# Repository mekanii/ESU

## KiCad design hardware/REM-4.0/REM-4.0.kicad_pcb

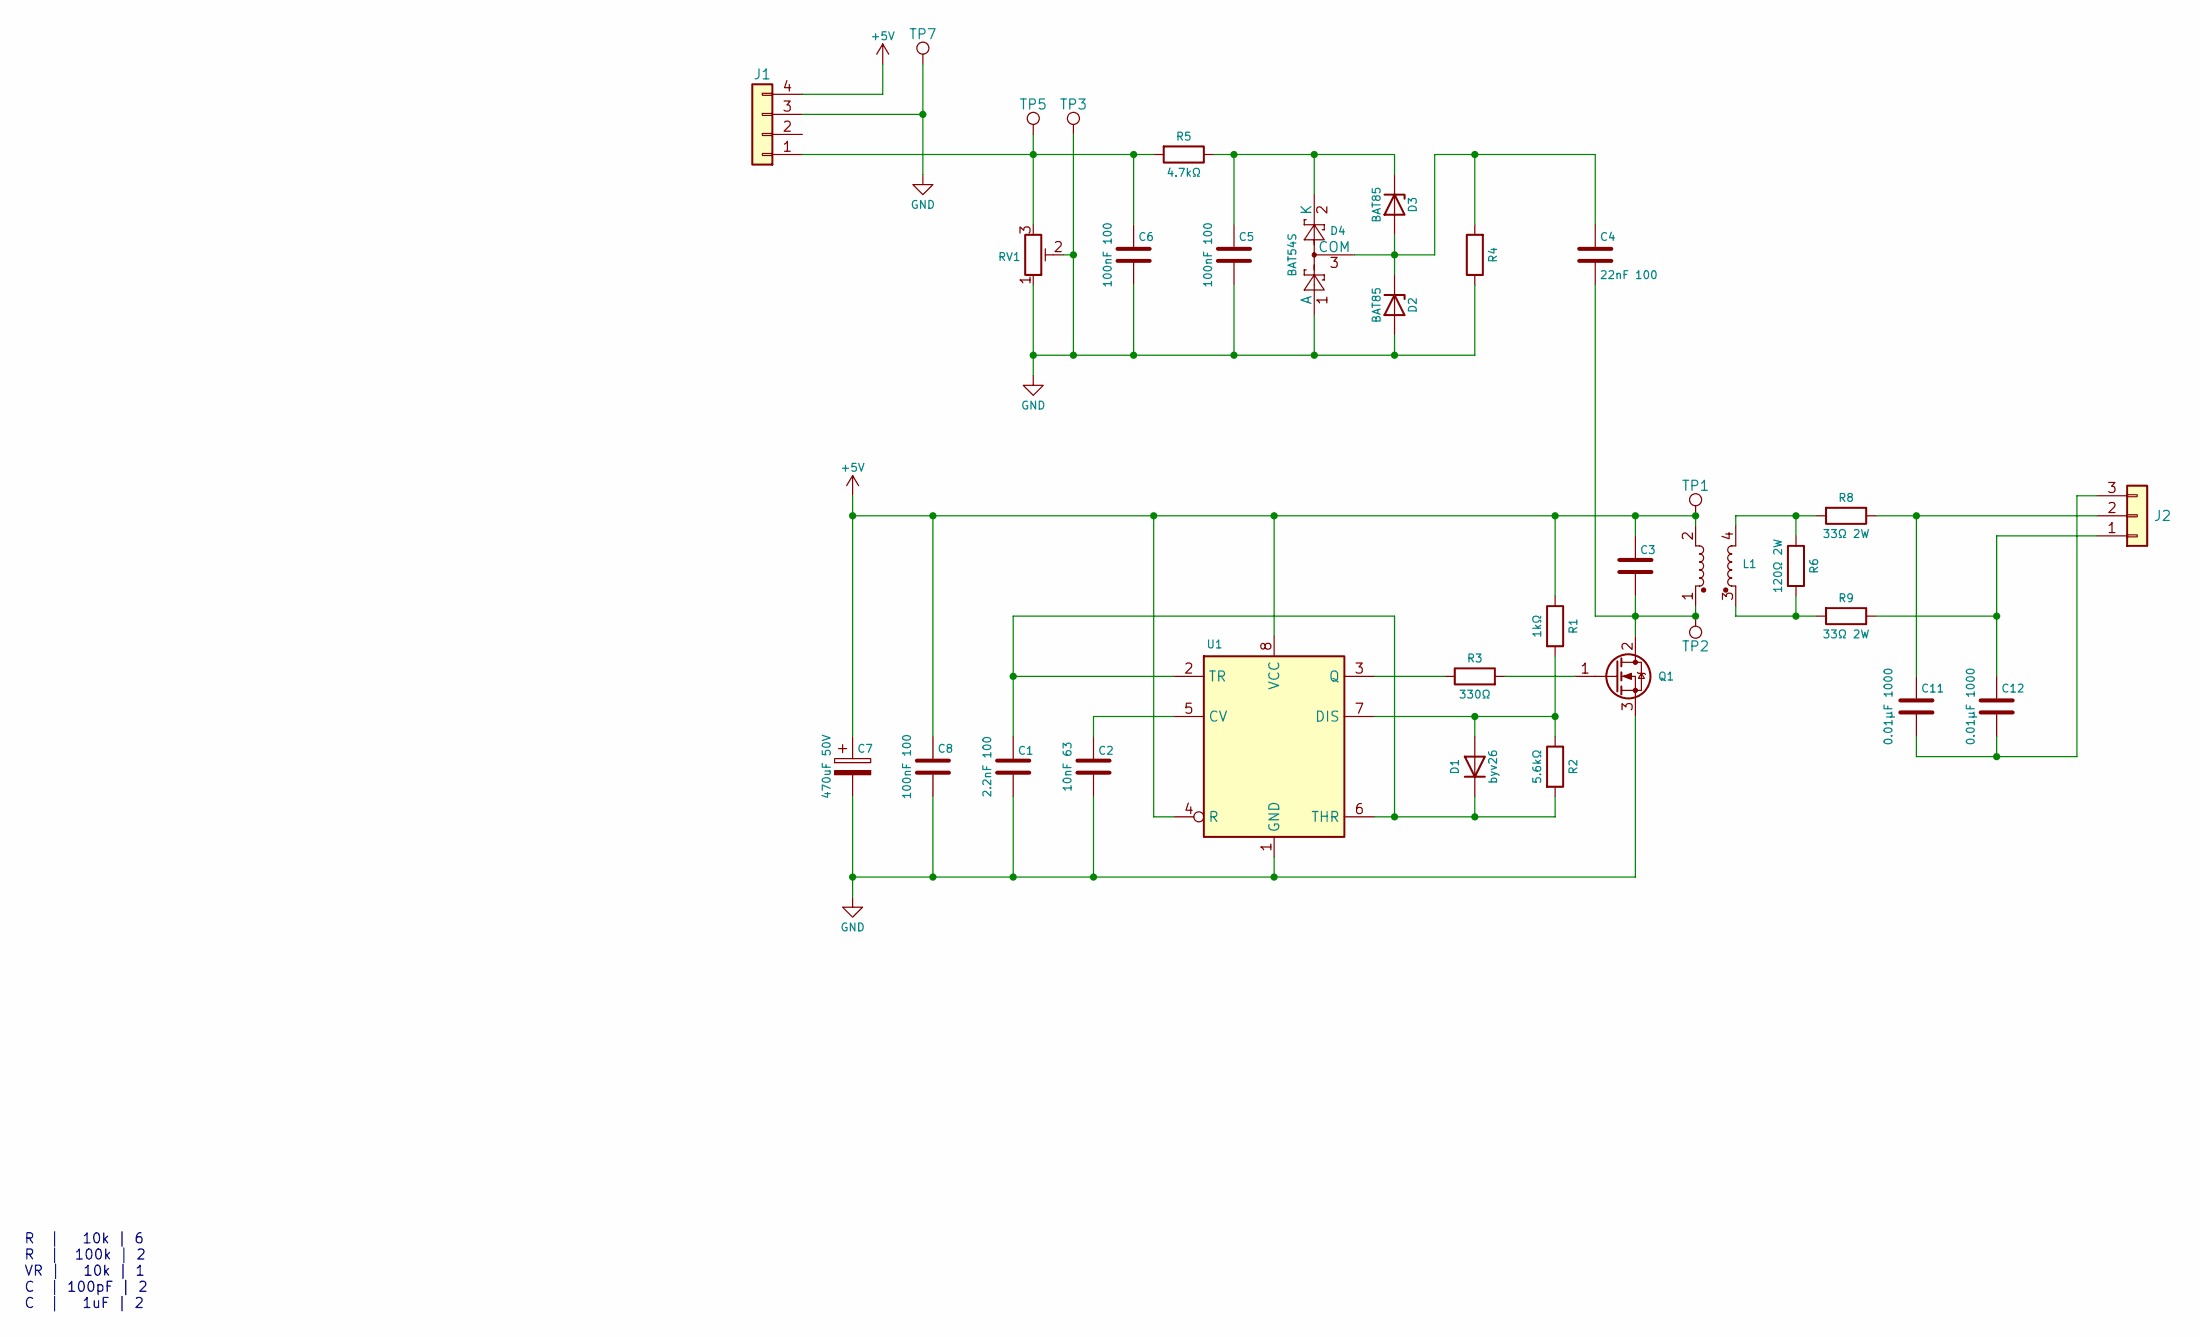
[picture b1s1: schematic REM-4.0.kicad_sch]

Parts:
C1: 2.2nF 100; C_Rect_L7.0mm_W3.5mm_P5.00mm
C2: 10nF 63; C_Rect_L7.0mm_W3.5mm_P5.00mm
C3: 0.022µF 400V; C_Rect_L13.0mm_W5.0mm_P10.00mm_FKS3_FKP3_MKS4
C4: 22nF 100; C_Rect_L7.0mm_W3.5mm_P5.00mm
C5, C6, C8: 100nF 100; C_Rect_L7.0mm_W3.5mm_P5.00mm
C7: 470uF 50V; CP_Radial_D12.5mm_P5.00mm
C11, C12: 0.01µF 1000; C_Rect_L13.0mm_W5.0mm_P10.00mm_FKS3_FKP3_MKS4
D1: byv26; D_DO-35_SOD27_P7.62mm_Horizontal
D2, D3: BAT85; D_DO-34_SOD68_P7.62mm_Horizontal
D4: BAT54S; SOT-23
J1: PinHeader_2.54mm 02x04 Horizontal; PinHeader_1x04_P2.54mm_Horizontal_2
J2: PinHeader_2.54mm 02x05 Horizontal; PinHeader_1x03_P5.08mm_Horizontal_2
L1: Isolated Transformer (Custom); L_CommonMode_Toroid_Horizontal_OD23mm_ID14mm_H8mm
Q1: IRLB3034PbF; TO-220-3_Horizontal_TabDown
R1: 1kΩ; R_Axial_DIN0204_L3.6mm_D1.6mm_P7.62mm_Horizontal
R2: 5.6kΩ; R_Axial_DIN0204_L3.6mm_D1.6mm_P7.62mm_Horizontal
R3: 330Ω; R_Axial_DIN0204_L3.6mm_D1.6mm_P7.62mm_Horizontal
R4: 10k; R_Axial_DIN0204_L3.6mm_D1.6mm_P7.62mm_Horizontal
R5: 4.7kΩ; R_Axial_DIN0204_L3.6mm_D1.6mm_P7.62mm_Horizontal
R6: 120Ω 2W; R_Axial_DIN0414_L11.9mm_D4.5mm_P20.32mm_Horizontal
R8, R9: 33Ω 2W; R_Axial_DIN0414_L11.9mm_D4.5mm_P20.32mm_Horizontal
RV1: 5kΩ; Potentiometer_Bourns_3296X_Horizontal
TP1, TP2, TP3, TP5, TP7: TestPoint_Bridge_Pitch2.54mm_Drill1.0mm
U1: NE555P; DIP-8_W7.62mm_Socket

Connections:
+5V: C3.1, C7.1, C8.1, J1.4, L1.2, R1.1, TP1.1, U1.4 (R), U1.8 (VCC)
GND: C1.2, C2.2, C5.2, C6.2, C7.2, C8.2, D2.2 (A), D4.1 (A), J1.3, Q1.3 (S), R4.1, RV1.1, RV1.2, TP3.1, TP7.1, U1.1 (GND)
unnamed: D1.2 (A), R1.2, R2.1, U1.7 (DIS)
unnamed: C1.1, D1.1 (K), R2.2, U1.2 (TR), U1.6 (THR)
unnamed: C4.1, D2.1 (K), D3.2 (A), D4.3 (COM), R4.2
unnamed: C5.1, D3.1 (K), D4.2 (K), R5.1
unnamed: C6.1, J1.1, R5.2, RV1.3, TP5.1
unnamed: C12.1, J2.1, R9.1
unnamed: C11.1, J2.2, R8.1
unnamed: C11.2, C12.2, J2.3
unnamed: L1.3, R6.2, R9.2
unnamed: L1.4, R6.1, R8.2
unnamed: C3.2, C4.2, L1.1, Q1.2 (D), TP2.1
unnamed: Q1.1 (G), R3.2
unnamed: C2.1, U1.5 (CV)
unnamed: R3.1, U1.3 (Q)

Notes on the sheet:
R | 10k | 6 R | 100k | 2 VR | 10k | 1 C | 100pF | 2 C | 1uF | 2

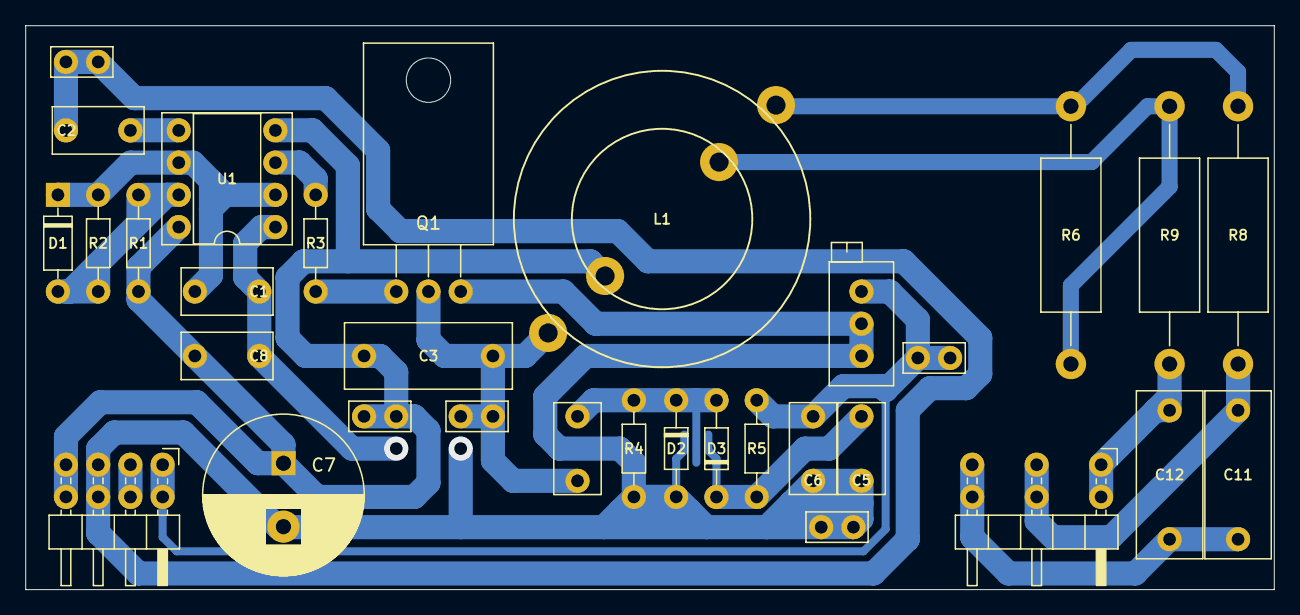
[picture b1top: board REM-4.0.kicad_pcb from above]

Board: 2 copper layers, 98.4 x 44.5 mm, 33 parts (1 on the bottom side), 16 nets.

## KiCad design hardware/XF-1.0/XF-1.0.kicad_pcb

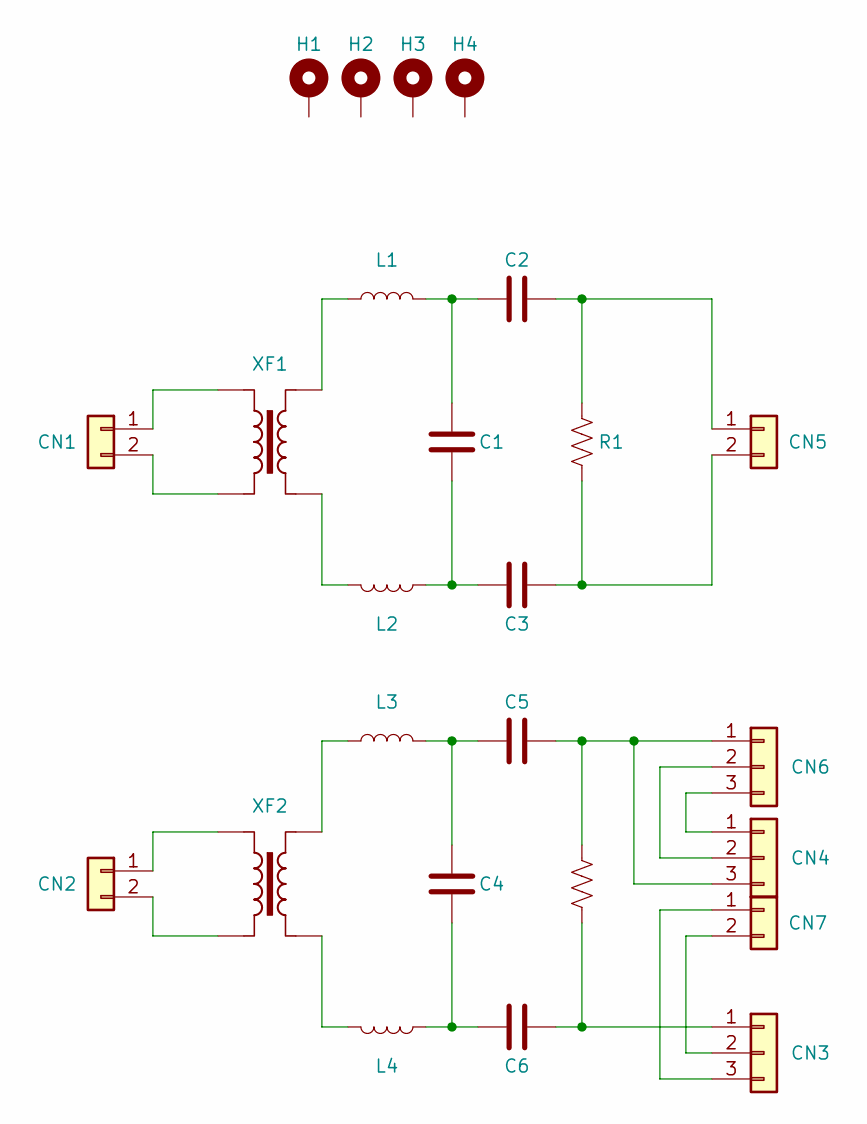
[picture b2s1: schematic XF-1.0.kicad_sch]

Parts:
C1, C4: 2.7nF; C_Axial_L12.0mm_D6.5mm_P20.00mm_Horizontal
C2, C3, C5, C6: 4.7nF; C_Rect_L13.0mm_W8.0mm_P10.00mm_FKS3_FKP3_MKS4
CN1, CN2, CN5, CN7: Conn_01x02; Molex_KK-396_5273-03A_1x03_P3.96mm_Vertical_2
CN3, CN4, CN6: Conn_01x03; Molex_KK-396_5273-05A_1x05_P3.96mm_Vertical_2
H1, H2, H3, H4: MountingHole_3mm_Pad
L1, L2, L3, L4: 29µH; L_Radial_Multilayer_D8.0mm_P12.70mm
R1, R2: RBTL
XF1, XF2: Transformer_Toroid_Horizontal_OD40_ID23_H15

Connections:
unnamed: C1.1, C2.1, L1.2
unnamed: C1.2, C3.1, L2.2
unnamed: C4.1, C5.1, L3.2
unnamed: C4.2, C6.1, L4.2
unnamed: CN1.1, XF1.1
unnamed: CN1.2, XF1.2
unnamed: CN2.1, XF2.1
unnamed: CN2.2, XF2.2
unnamed: C6.2, CN3.1, R2.2
unnamed: CN3.2, CN7.2
unnamed: CN3.3, CN7.1
unnamed: CN4.1, CN6.3
unnamed: CN4.2, CN6.2
unnamed: C5.2, CN4.3, CN6.1, R2.1
unnamed: C2.2, CN5.1, R1.1
unnamed: C3.2, CN5.2, R1.2
unnamed: L1.1, XF1.4
unnamed: L2.1, XF1.3
unnamed: L3.1, XF2.4
unnamed: L4.1, XF2.3

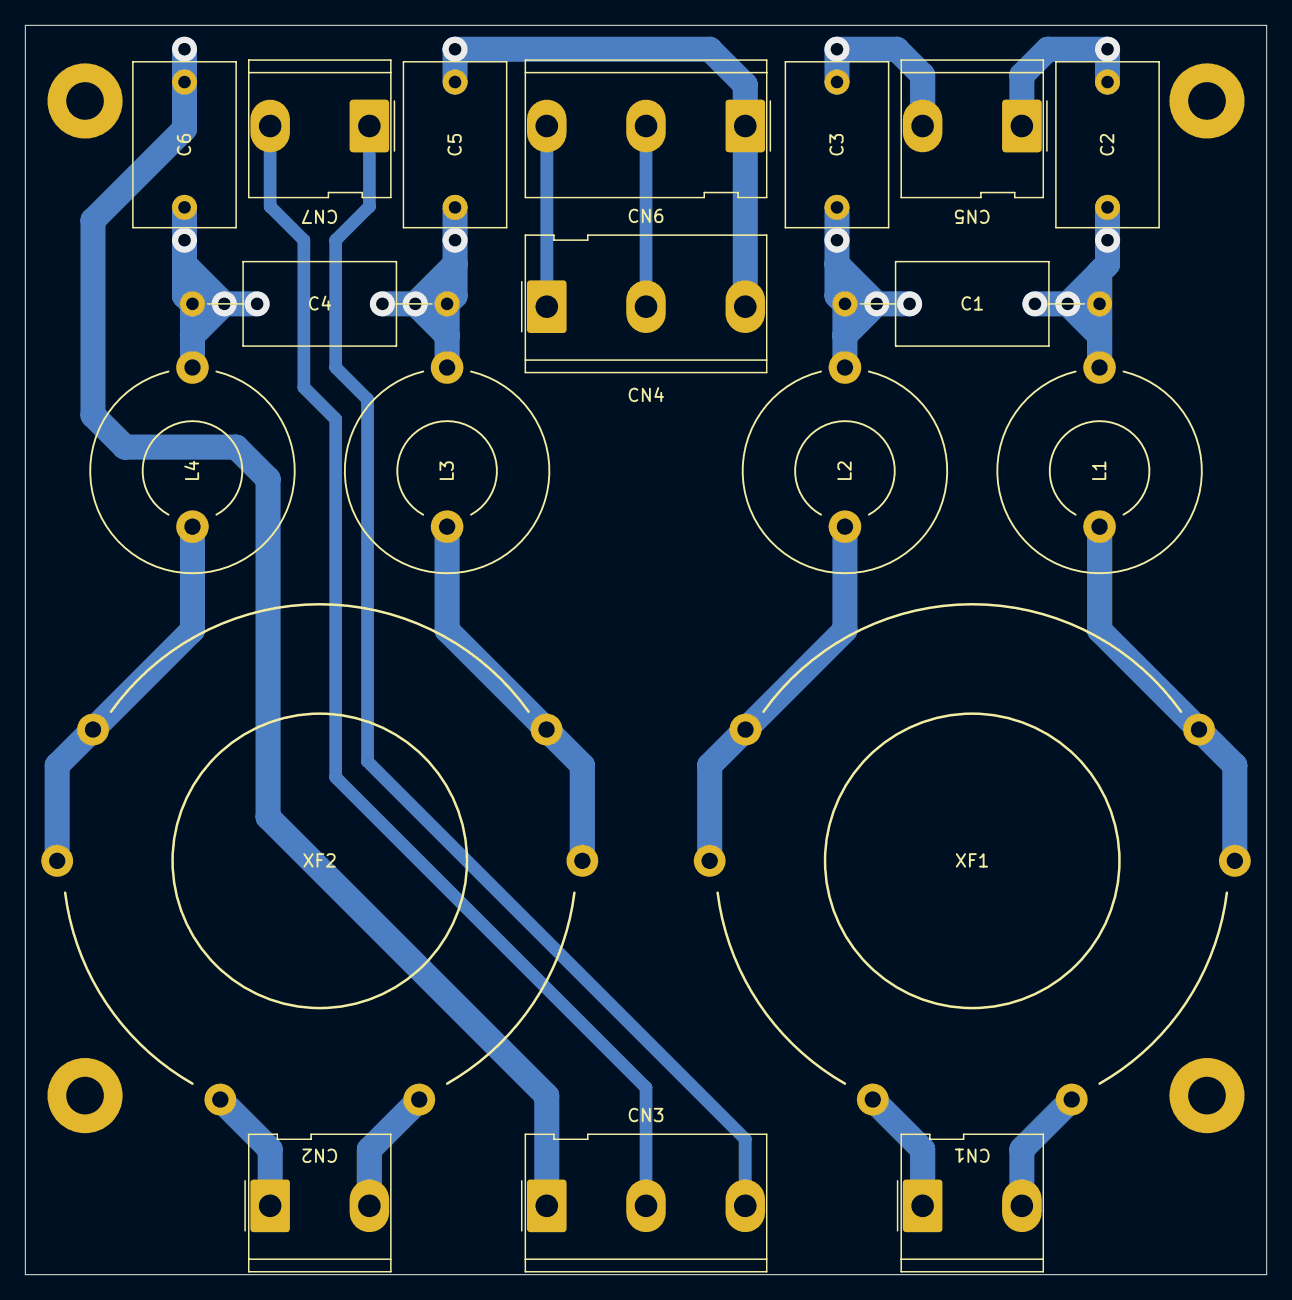
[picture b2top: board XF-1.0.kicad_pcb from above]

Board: 2 copper layers, 99.1 x 99.7 mm, 23 parts (0 on the bottom side), 20 nets.

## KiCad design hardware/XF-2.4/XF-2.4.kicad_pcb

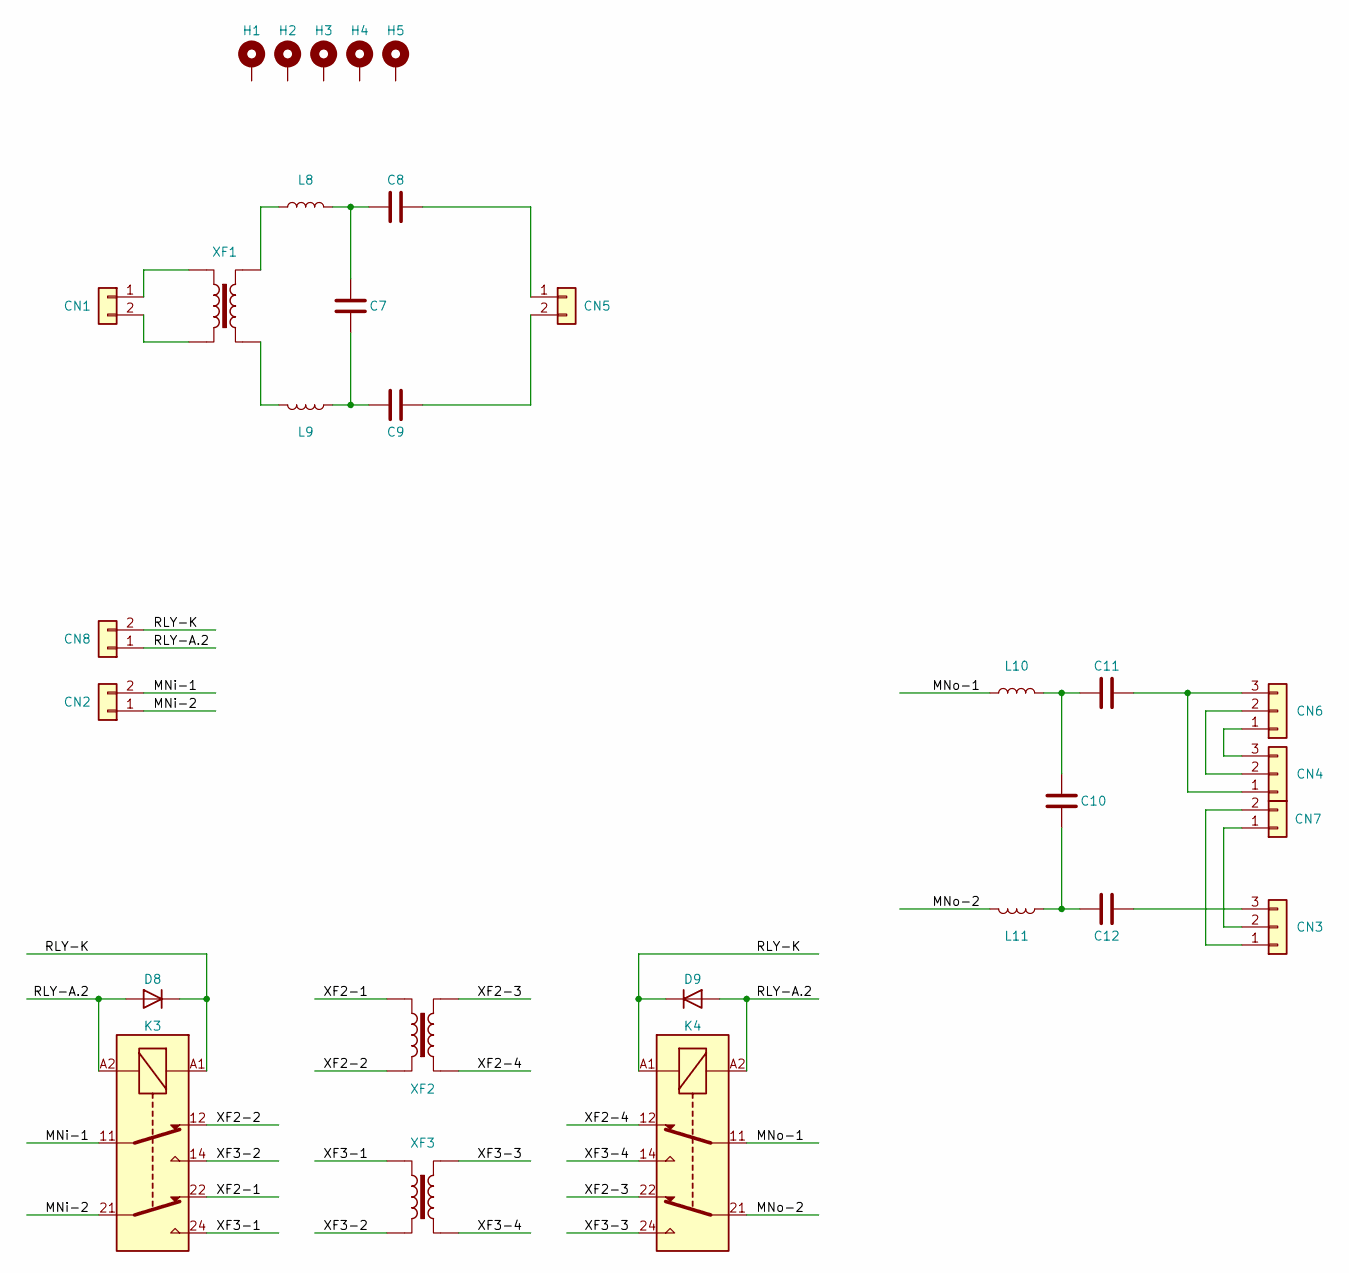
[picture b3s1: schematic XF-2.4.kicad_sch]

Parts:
C7, C10: 2.7nF; C_Axial_L12.0mm_D6.5mm_P15.00mm_Horizontal
C8, C9, C11, C12: 4.7nF; C_Rect_L13.0mm_W8.0mm_P10.00mm_FKS3_FKP3_MKS4
CN1, CN2, CN5, CN7: Conn_01x02; Molex_KK-396_5273-03A_1x03_P3.96mm_Vertical_2
CN3, CN4, CN6: Conn_01x03; Molex_KK-396_5273-05A_1x05_P3.96mm_Vertical_2
CN8: Conn_01x02; Molex_KK-396_5273-02A_1x02_P3.96mm_Vertical
D8, D9: 1N4148; D_DO-35_SOD27_P7.62mm_Horizontal
H1, H2, H3, H4, H5: MountingHole_3mm_Pad
K3, K4: G2RL-2; Relay_DPDT_Omron_G2RL-2
L8, L9, L10, L11: 29µH; L_Radial_Multilayer_D8.0mm_P12.70mm
XF1, XF2, XF3: Transformer_Toroid_Horizontal_OD40_ID23_H15

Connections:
/MNi-1: CN2.2, K3.11
/MNi-2: CN2.1, K3.21
/MNo-1: K4.11, L10.1
/MNo-2: K4.21, L11.1
/RLY-A.2: CN8.1, D8.2 (A), D9.2 (A), K3.A2, K4.A2
/RLY-K: CN8.2, D8.1 (K), D9.1 (K), K3.A1, K4.A1
/XF2-1: K3.22, XF2.2
/XF2-2: K3.12, XF2.1
/XF2-3: K4.22, XF2.3
/XF2-4: K4.12, XF2.4
/XF3-1: K3.24, XF3.1
/XF3-2: K3.14, XF3.2
/XF3-3: K4.24, XF3.4
/XF3-4: K4.14, XF3.3
unnamed: C7.1, C8.1, L8.2
unnamed: C7.2, C9.1, L9.2
unnamed: C10.1, C11.1, L10.2
unnamed: C10.2, C12.1, L11.2
unnamed: CN1.1, XF1.1
unnamed: CN1.2, XF1.2
unnamed: CN3.1, CN7.2
unnamed: CN3.2, CN7.1
unnamed: C12.2, CN3.3
unnamed: C11.2, CN4.1, CN6.3
unnamed: CN4.2, CN6.2
unnamed: CN4.3, CN6.1
unnamed: C8.2, CN5.1
unnamed: C9.2, CN5.2
unnamed: L8.1, XF1.4
unnamed: L9.1, XF1.3

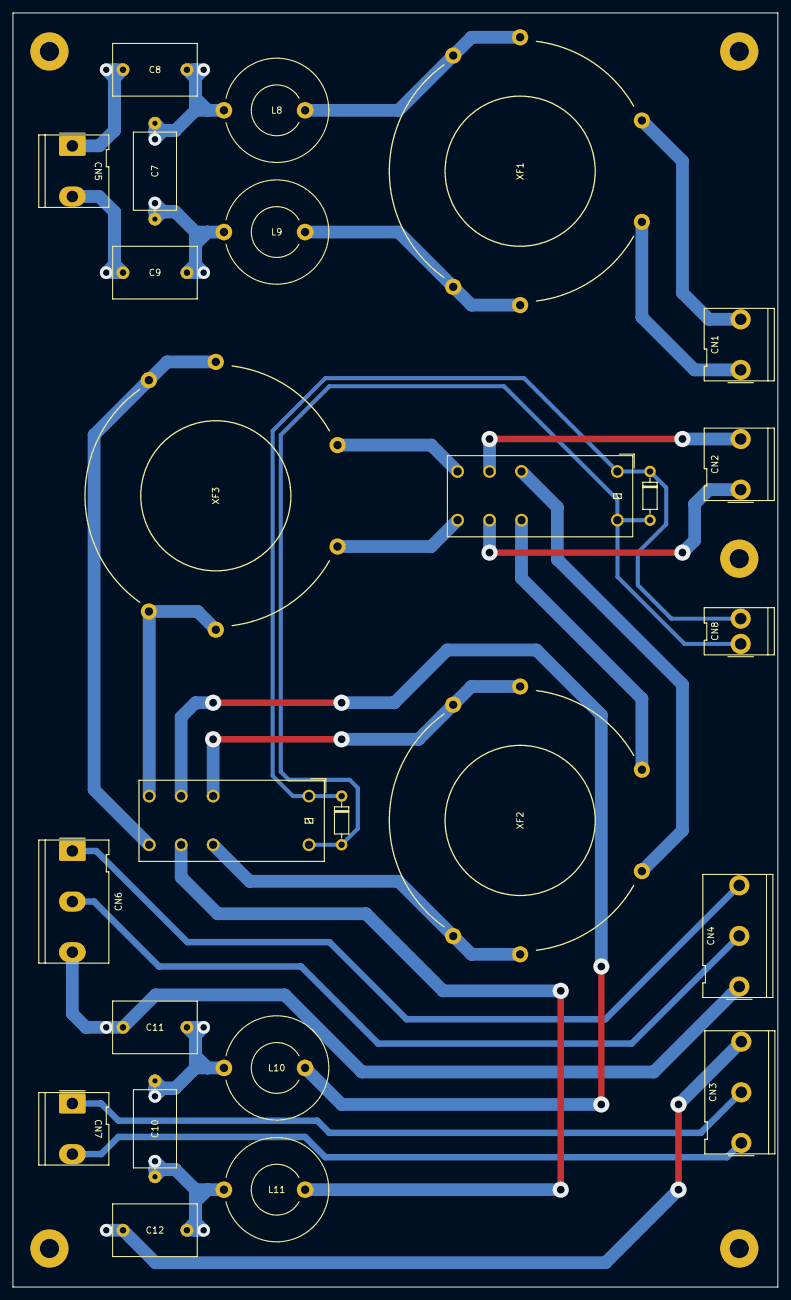
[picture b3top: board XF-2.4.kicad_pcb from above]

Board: 2 copper layers, 119.7 x 199.4 mm, 30 parts (0 on the bottom side), 30 nets.
